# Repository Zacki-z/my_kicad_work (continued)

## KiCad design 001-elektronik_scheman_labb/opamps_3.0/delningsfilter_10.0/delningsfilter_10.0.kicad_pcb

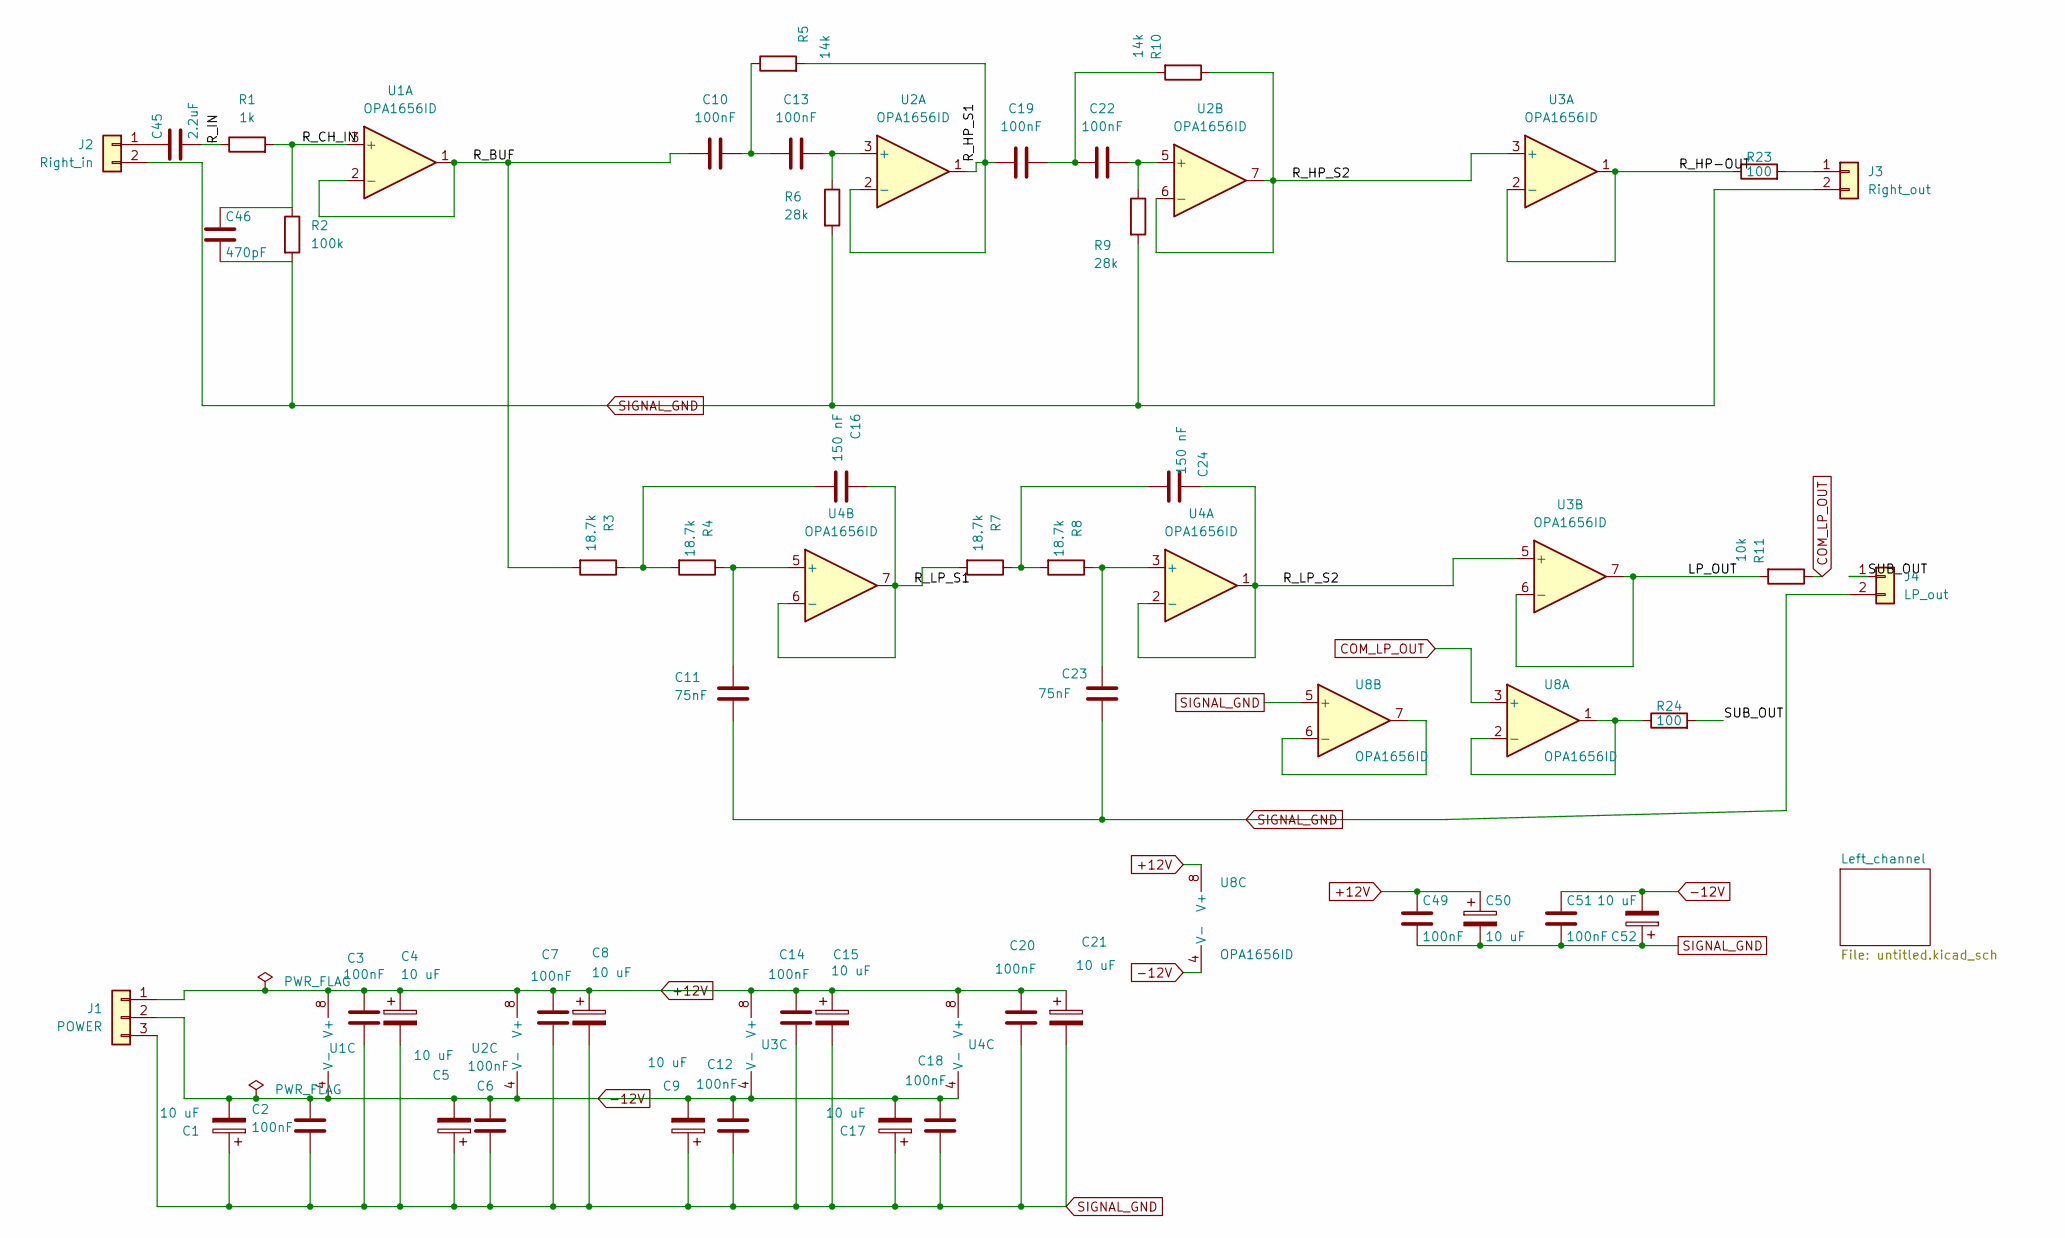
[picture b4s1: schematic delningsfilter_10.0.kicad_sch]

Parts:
C1, C4, C5, C8, C9, C15, C17, C21, C50, C52: 10 uF; CP_Radial_D5.0mm_P2.00mm
C2, C3, C6, C7, C10, C12, C13, C14, C18, C19, C20, C22, C49, C51: 100nF; C_Disc_D5.0mm_W2.5mm_P2.50mm
C11, C23: 75nF; C_Disc_D5.0mm_W2.5mm_P2.50mm
C16, C24: 150 nF; C_Disc_D5.0mm_W2.5mm_P2.50mm
C45: 2.2uF; C_Rect_L7.2mm_W3.5mm_P5.00mm_FKS2_FKP2_MKS2_MKP2
C46: 470pF; C_Disc_D5.0mm_W2.5mm_P2.50mm
J1: POWER; PinHeader_1x03_P2.54mm_Vertical; Part Number 1-0301FBV0T
J2: Right_in; PinHeader_1x02_P2.54mm_Vertical; Part Number 1-0201FBV0T
J3: Right_out; PinHeader_1x02_P2.54mm_Vertical; Part Number 1-0201FBV0T
J4: LP_out; PinHeader_1x02_P2.54mm_Vertical; Part Number 1-0201FBV0T
R1: 1k; R_Axial_DIN0207_L6.3mm_D2.5mm_P7.62mm_Horizontal
R2: 100k; R_Axial_DIN0207_L6.3mm_D2.5mm_P7.62mm_Horizontal
R3, R4, R7, R8: 18.7k; R_Axial_DIN0207_L6.3mm_D2.5mm_P7.62mm_Horizontal
R5, R10: 14k; R_Axial_DIN0207_L6.3mm_D2.5mm_P7.62mm_Horizontal
R6, R9: 28k; R_Axial_DIN0207_L6.3mm_D2.5mm_P7.62mm_Horizontal
R11: 10k; R_Axial_DIN0207_L6.3mm_D2.5mm_P7.62mm_Horizontal
R23, R24: 100; R_Axial_DIN0207_L6.3mm_D2.5mm_P7.62mm_Horizontal
U1, U2, U3, U4, U8: OPA1656ID; DIP-8_W7.62mm

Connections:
+12V: C3.1, C4.1, C7.1, C8.1, C14.1, C15.1, C20.1, C21.1, C49.1, C50.1, J1.1, U1.8 (V+), U2.8 (V+), U3.8 (V+), U4.8 (V+), U8.8 (V+); also elsewhere on the board
-12V: C1.2, C2.1, C5.2, C6.1, C9.2, C12.1, C17.2, C18.1, C51.1, C52.2, J1.2, U1.4 (V-), U2.4 (V-), U3.4 (V-), U4.4 (V-), U8.4 (V-); also elsewhere on the board
/LP_OUT: R11.2, U3.6 (-), U3.7
/R_BUF: C10.2, R3.2, U1.1, U1.2 (-)
/R_CH_IN: C46.1, R1.2, R2.1, U1.3 (+)
/R_HP-OUT: R23.1, U3.1, U3.2 (-)
/R_HP_S1: C19.2, R5.2, U2.1, U2.2 (-)
/R_HP_S2: R10.1, U2.6 (-), U2.7, U3.3 (+)
/R_IN: C45.2, R1.1
/R_LP_S1: C16.1, R7.2, U4.6 (-), U4.7
/R_LP_S2: C24.2, U3.5 (+), U4.1, U4.2 (-)
/SUB_OUT: J4.1, R24.2
COM_LP_OUT: R11.1, U8.3 (+); also elsewhere on the board
unnamed: C10.1, C13.2, R5.1
unnamed: C16.2, R3.1, R4.2
unnamed: C19.1, C22.2, R10.2
unnamed: C24.1, R7.1, R8.2
unnamed: C45.1, J2.1
unnamed: J3.1, R23.2
unnamed: C13.1, R6.1, U2.3 (+)
unnamed: C22.1, R9.1, U2.5 (+)
unnamed: C23.1, R8.1, U4.3 (+)
unnamed: C11.1, R4.1, U4.5 (+)
unnamed: R24.1, U8.1, U8.2 (-)
unnamed: U8.6 (-), U8.7
SIGNAL_GND: C1.1, C2.2, C3.2, C4.2, C5.1, C6.2, C7.2, C8.2, C9.1, C11.2, C12.2, C14.2, C15.2, C17.1, C18.2, C20.2, C21.2, C23.2, C46.2, C49.2, C50.2, C51.2, C52.1, J1.3, J2.2, J3.2, J4.2, R2.2, R6.2, R9.2, U8.5 (+); also elsewhere on the board

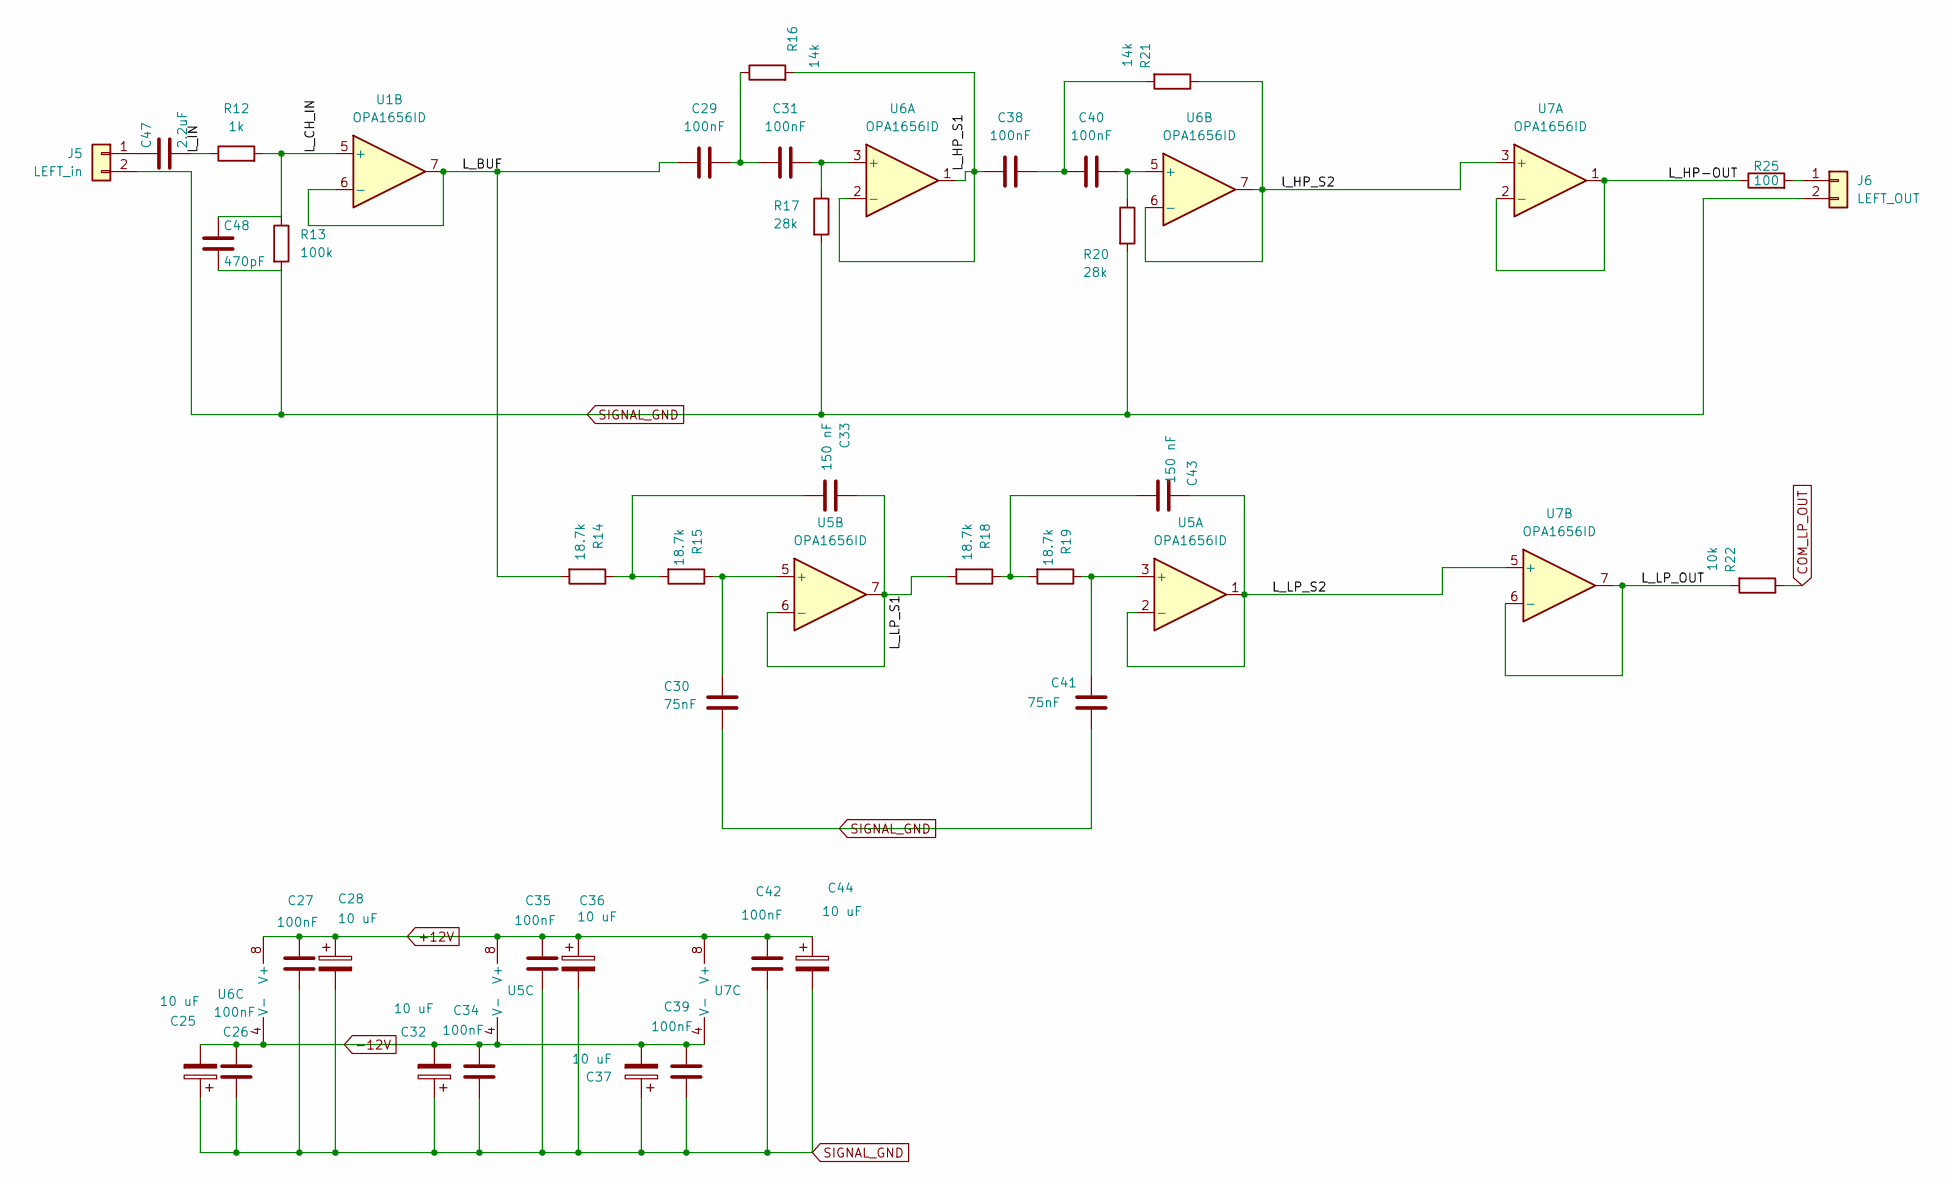
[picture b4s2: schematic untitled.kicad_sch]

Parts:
C25, C32, C36, C37, C44: 10 uF; CP_Radial_D5.0mm_P2.00mm
C26, C27, C29, C31, C34, C35, C38, C39, C40, C42: 100nF; C_Disc_D5.0mm_W2.5mm_P2.50mm
C28: 10 uF; CP_Radial_D5.0mm_P2.50mm
C30, C41: 75nF; C_Disc_D5.0mm_W2.5mm_P2.50mm
C33, C43: 150 nF; C_Disc_D5.0mm_W2.5mm_P2.50mm
C47: 2.2uF; C_Rect_L7.2mm_W3.5mm_P5.00mm_FKS2_FKP2_MKS2_MKP2
C48: 470pF; C_Disc_D5.0mm_W2.5mm_P2.50mm
J5: LEFT_in; PinHeader_1x02_P2.54mm_Vertical; Part Number 1-0201FBV0T
J6: LEFT_OUT; PinHeader_1x02_P2.54mm_Vertical; Part Number 1-0201FBV0T
R12: 1k; R_Axial_DIN0207_L6.3mm_D2.5mm_P7.62mm_Horizontal
R13: 100k; R_Axial_DIN0207_L6.3mm_D2.5mm_P7.62mm_Horizontal
R14, R15, R18, R19: 18.7k; R_Axial_DIN0207_L6.3mm_D2.5mm_P7.62mm_Horizontal
R16, R21: 14k; R_Axial_DIN0207_L6.3mm_D2.5mm_P7.62mm_Horizontal
R17, R20: 28k; R_Axial_DIN0207_L6.3mm_D2.5mm_P7.62mm_Horizontal
R22: 10k; R_Axial_DIN0207_L6.3mm_D2.5mm_P7.62mm_Horizontal
R25: 100; R_Axial_DIN0207_L6.3mm_D2.5mm_P7.62mm_Horizontal
U1, U5, U6, U7: OPA1656ID; DIP-8_W7.62mm

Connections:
+12V: C27.1, C28.1, C35.1, C36.1, C42.1, C44.1, U5.8 (V+), U6.8 (V+), U7.8 (V+); also elsewhere on the board
-12V: C25.2, C26.1, C32.2, C34.1, C37.2, C39.1, U5.4 (V-), U6.4 (V-), U7.4 (V-); also elsewhere on the board
/Left_channel/L_BUF: C29.2, R14.2, U1.6 (-), U1.7
/Left_channel/L_CH_IN: C48.1, R12.2, R13.1, U1.5 (+)
/Left_channel/L_HP-OUT: R25.1, U7.1, U7.2 (-)
/Left_channel/L_HP_S1: C38.2, R16.2, U6.1, U6.2 (-)
/Left_channel/L_IN: C47.2, R12.1
/Left_channel/L_LP_OUT: R22.2, U7.6 (-), U7.7
/Left_channel/L_LP_S1: C33.1, R18.2, U5.6 (-), U5.7
/Left_channel/L_LP_S2: C43.2, U5.1, U5.2 (-), U7.5 (+)
/Left_channel/l_HP_S2: R21.1, U6.6 (-), U6.7, U7.3 (+)
COM_LP_OUT: R22.1; also elsewhere on the board
unnamed: C29.1, C31.2, R16.1
unnamed: C33.2, R14.1, R15.2
unnamed: C38.1, C40.2, R21.2
unnamed: C43.1, R18.1, R19.2
unnamed: C47.1, J5.1
unnamed: J6.1, R25.2
unnamed: C41.1, R19.1, U5.3 (+)
unnamed: C30.1, R15.1, U5.5 (+)
unnamed: C31.1, R17.1, U6.3 (+)
unnamed: C40.1, R20.1, U6.5 (+)
SIGNAL_GND: C25.1, C26.2, C27.2, C28.2, C30.2, C32.1, C34.2, C35.2, C36.2, C37.1, C39.2, C41.2, C42.2, C44.2, C48.2, J5.2, J6.2, R13.2, R17.2, R20.2; also elsewhere on the board

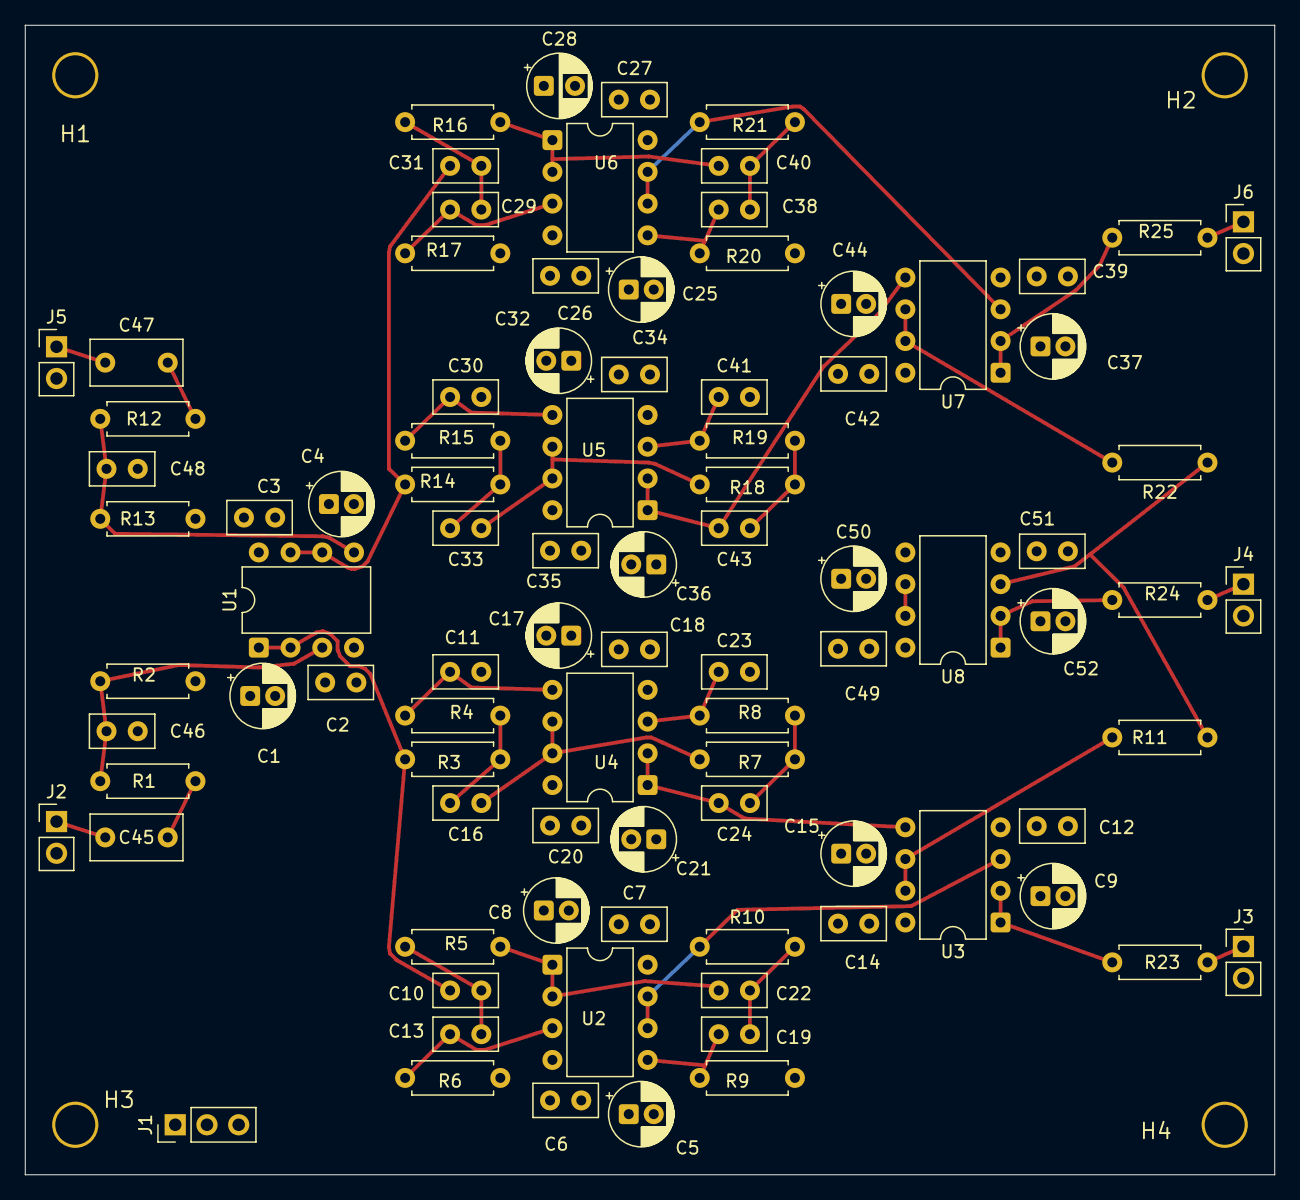
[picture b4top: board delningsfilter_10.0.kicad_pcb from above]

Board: 4 copper layers, 100.0 x 92.0 mm, 95 parts (0 on the bottom side), 45 nets.

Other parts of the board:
H1, H2, H3, H4: MountingHole; MountingHole_3.2mm

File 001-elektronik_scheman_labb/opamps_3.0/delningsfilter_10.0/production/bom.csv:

"Refs","Value","Footprint","Qty","DNP"
"C1","10 uF","Capacitor_THT:CP_Radial_D5.0mm_P2.00mm","1",""
"C2","100nF","Capacitor_THT:C_Disc_D5.0mm_W2.5mm_P2.50mm","1",""
"C3","100nF","Capacitor_THT:C_Disc_D5.0mm_W2.5mm_P2.50mm","1",""
"C4","10 uF","Capacitor_THT:CP_Radial_D5.0mm_P2.00mm","1",""
"C5","10 uF","Capacitor_THT:CP_Radial_D5.0mm_P2.00mm","1",""
"C6","100nF","Capacitor_THT:C_Disc_D5.0mm_W2.5mm_P2.50mm","1",""
"C7","100nF","Capacitor_THT:C_Disc_D5.0mm_W2.5mm_P2.50mm","1",""
"C8","10 uF","Capacitor_THT:CP_Radial_D5.0mm_P2.00mm","1",""
"C9","10 uF","Capacitor_THT:CP_Radial_D5.0mm_P2.00mm","1",""
"C10","100nF","Capacitor_THT:C_Disc_D5.0mm_W2.5mm_P2.50mm","1",""
"C11","75nF","Capacitor_THT:C_Disc_D5.0mm_W2.5mm_P2.50mm","1",""
"C12","100nF","Capacitor_THT:C_Disc_D5.0mm_W2.5mm_P2.50mm","1",""
"C13","100nF","Capacitor_THT:C_Disc_D5.0mm_W2.5mm_P2.50mm","1",""
"C14","100nF","Capacitor_THT:C_Disc_D5.0mm_W2.5mm_P2.50mm","1",""
"C15","10 uF","Capacitor_THT:CP_Radial_D5.0mm_P2.00mm","1",""
"C16","150 nF","Capacitor_THT:C_Disc_D5.0mm_W2.5mm_P2.50mm","1",""
"C17","10 uF","Capacitor_THT:CP_Radial_D5.0mm_P2.00mm","1",""
"C18","100nF","Capacitor_THT:C_Disc_D5.0mm_W2.5mm_P2.50mm","1",""
"C19","100nF","Capacitor_THT:C_Disc_D5.0mm_W2.5mm_P2.50mm","1",""
"C20","100nF","Capacitor_THT:C_Disc_D5.0mm_W2.5mm_P2.50mm","1",""
"C21","10 uF","Capacitor_THT:CP_Radial_D5.0mm_P2.00mm","1",""
"C22","100nF","Capacitor_THT:C_Disc_D5.0mm_W2.5mm_P2.50mm","1",""
"C23","75nF","Capacitor_THT:C_Disc_D5.0mm_W2.5mm_P2.50mm","1",""
"C24","150 nF","Capacitor_THT:C_Disc_D5.0mm_W2.5mm_P2.50mm","1",""
"C25","10 uF","Capacitor_THT:CP_Radial_D5.0mm_P2.00mm","1",""
"C26","100nF","Capacitor_THT:C_Disc_D5.0mm_W2.5mm_P2.50mm","1",""
"C27","100nF","Capacitor_THT:C_Disc_D5.0mm_W2.5mm_P2.50mm","1",""
"C28","10 uF","Capacitor_THT:CP_Radial_D5.0mm_P2.50mm","1",""
"C29","100nF","Capacitor_THT:C_Disc_D5.0mm_W2.5mm_P2.50mm","1",""
"C30","75nF","Capacitor_THT:C_Disc_D5.0mm_W2.5mm_P2.50mm","1",""
"C31","100nF","Capacitor_THT:C_Disc_D5.0mm_W2.5mm_P2.50mm","1",""
"C32","10 uF","Capacitor_THT:CP_Radial_D5.0mm_P2.00mm","1",""
"C33","150 nF","Capacitor_THT:C_Disc_D5.0mm_W2.5mm_P2.50mm","1",""
"C34","100nF","Capacitor_THT:C_Disc_D5.0mm_W2.5mm_P2.50mm","1",""
"C35","100nF","Capacitor_THT:C_Disc_D5.0mm_W2.5mm_P2.50mm","1",""
"C36","10 uF","Capacitor_THT:CP_Radial_D5.0mm_P2.00mm","1",""
"C37","10 uF","Capacitor_THT:CP_Radial_D5.0mm_P2.00mm","1",""
"C38","100nF","Capacitor_THT:C_Disc_D5.0mm_W2.5mm_P2.50mm","1",""
"C39","100nF","Capacitor_THT:C_Disc_D5.0mm_W2.5mm_P2.50mm","1",""
"C40","100nF","Capacitor_THT:C_Disc_D5.0mm_W2.5mm_P2.50mm","1",""
"C41","75nF","Capacitor_THT:C_Disc_D5.0mm_W2.5mm_P2.50mm","1",""
"C42","100nF","Capacitor_THT:C_Disc_D5.0mm_W2.5mm_P2.50mm","1",""
"C43","150 nF","Capacitor_THT:C_Disc_D5.0mm_W2.5mm_P2.50mm","1",""
"C44","10 uF","Capacitor_THT:CP_Radial_D5.0mm_P2.00mm","1",""
"C45","2.2uF","Capacitor_THT:C_Rect_L7.2mm_W3.5mm_P5.00mm_FKS2_FKP2_MKS2_MKP2","1",""
"C46","470pF","Capacitor_THT:C_Disc_D5.0mm_W2.5mm_P2.50mm","1",""
"C47","2.2uF","Capacitor_THT:C_Rect_L7.2mm_W3.5mm_P5.00mm_FKS2_FKP2_MKS2_MKP2","1",""
"C48","470pF","Capacitor_THT:C_Disc_D5.0mm_W2.5mm_P2.50mm","1",""
"C49","100nF","Capacitor_THT:C_Disc_D5.0mm_W2.5mm_P2.50mm","1",""
"C50","10 uF","Capacitor_THT:CP_Radial_D5.0mm_P2.00mm","1",""
"C51","100nF","Capacitor_THT:C_Disc_D5.0mm_W2.5mm_P2.50mm","1",""
"C52","10 uF","Capacitor_THT:CP_Radial_D5.0mm_P2.00mm","1",""
"J1","POWER","Connector_PinHeader_2.54mm:PinHeader_1x03_P2.54mm_Vertical","1",""
"J2","Right_in","Connector_PinHeader_2.54mm:PinHeader_1x02_P2.54mm_Vertical","1",""
"J3","Right_out","Connector_PinHeader_2.54mm:PinHeader_1x02_P2.54mm_Vertical","1",""
"J4","LP_out","Connector_PinHeader_2.54mm:PinHeader_1x02_P2.54mm_Vertical","1",""
"J5","LEFT_in","Connector_PinHeader_2.54mm:PinHeader_1x02_P2.54mm_Vertical","1",""
"J6","LEFT_OUT","Connector_PinHeader_2.54mm:PinHeader_1x02_P2.54mm_Vertical","1",""
"R1","1k","Resistor_THT:R_Axial_DIN0207_L6.3mm_D2.5mm_P7.62mm_Horizontal","1",""
"R2","100k","Resistor_THT:R_Axial_DIN0207_L6.3mm_D2.5mm_P7.62mm_Horizontal","1",""
"R3","18.7k","Resistor_THT:R_Axial_DIN0207_L6.3mm_D2.5mm_P7.62mm_Horizontal","1",""
"R4","18.7k","Resistor_THT:R_Axial_DIN0207_L6.3mm_D2.5mm_P7.62mm_Horizontal","1",""
"R5","14k","Resistor_THT:R_Axial_DIN0207_L6.3mm_D2.5mm_P7.62mm_Horizontal","1",""
"R6","28k","Resistor_THT:R_Axial_DIN0207_L6.3mm_D2.5mm_P7.62mm_Horizontal","1",""
"R7","18.7k","Resistor_THT:R_Axial_DIN0207_L6.3mm_D2.5mm_P7.62mm_Horizontal","1",""
"R8","18.7k","Resistor_THT:R_Axial_DIN0207_L6.3mm_D2.5mm_P7.62mm_Horizontal","1",""
"R9","28k","Resistor_THT:R_Axial_DIN0207_L6.3mm_D2.5mm_P7.62mm_Horizontal","1",""
"R10","14k","Resistor_THT:R_Axial_DIN0207_L6.3mm_D2.5mm_P7.62mm_Horizontal","1",""
"R11","10k","Resistor_THT:R_Axial_DIN0207_L6.3mm_D2.5mm_P7.62mm_Horizontal","1",""
"R12","1k","Resistor_THT:R_Axial_DIN0207_L6.3mm_D2.5mm_P7.62mm_Horizontal","1",""
"R13","100k","Resistor_THT:R_Axial_DIN0207_L6.3mm_D2.5mm_P7.62mm_Horizontal","1",""
"R14","18.7k","Resistor_THT:R_Axial_DIN0207_L6.3mm_D2.5mm_P7.62mm_Horizontal","1",""
"R15","18.7k","Resistor_THT:R_Axial_DIN0207_L6.3mm_D2.5mm_P7.62mm_Horizontal","1",""
"R16","14k","Resistor_THT:R_Axial_DIN0207_L6.3mm_D2.5mm_P7.62mm_Horizontal","1",""
"R17","28k","Resistor_THT:R_Axial_DIN0207_L6.3mm_D2.5mm_P7.62mm_Horizontal","1",""
"R18","18.7k","Resistor_THT:R_Axial_DIN0207_L6.3mm_D2.5mm_P7.62mm_Horizontal","1",""
"R19","18.7k","Resistor_THT:R_Axial_DIN0207_L6.3mm_D2.5mm_P7.62mm_Horizontal","1",""
"R20","28k","Resistor_THT:R_Axial_DIN0207_L6.3mm_D2.5mm_P7.62mm_Horizontal","1",""
"R21","14k","Resistor_THT:R_Axial_DIN0207_L6.3mm_D2.5mm_P7.62mm_Horizontal","1",""
"R22","10k","Resistor_THT:R_Axial_DIN0207_L6.3mm_D2.5mm_P7.62mm_Horizontal","1",""
"R23","100","Resistor_THT:R_Axial_DIN0207_L6.3mm_D2.5mm_P7.62mm_Horizontal","1",""
"R24","100","Resistor_THT:R_Axial_DIN0207_L6.3mm_D2.5mm_P7.62mm_Horizontal","1",""
"R25","100","Resistor_THT:R_Axial_DIN0207_L6.3mm_D2.5mm_P7.62mm_Horizontal","1",""
"U1","OPA1656ID","Package_DIP:DIP-8_W7.62mm","1",""
"U2","OPA1656ID","Package_DIP:DIP-8_W7.62mm","1",""
"U3","OPA1656ID","Package_DIP:DIP-8_W7.62mm","1",""
"U4","OPA1656ID","Package_DIP:DIP-8_W7.62mm","1",""
"U5","OPA1656ID","Package_DIP:DIP-8_W7.62mm","1",""
"U6","OPA1656ID","Package_DIP:DIP-8_W7.62mm","1",""
"U7","OPA1656ID","Package_DIP:DIP-8_W7.62mm","1",""
"U8","OPA1656ID","Package_DIP:DIP-8_W7.62mm","1",""

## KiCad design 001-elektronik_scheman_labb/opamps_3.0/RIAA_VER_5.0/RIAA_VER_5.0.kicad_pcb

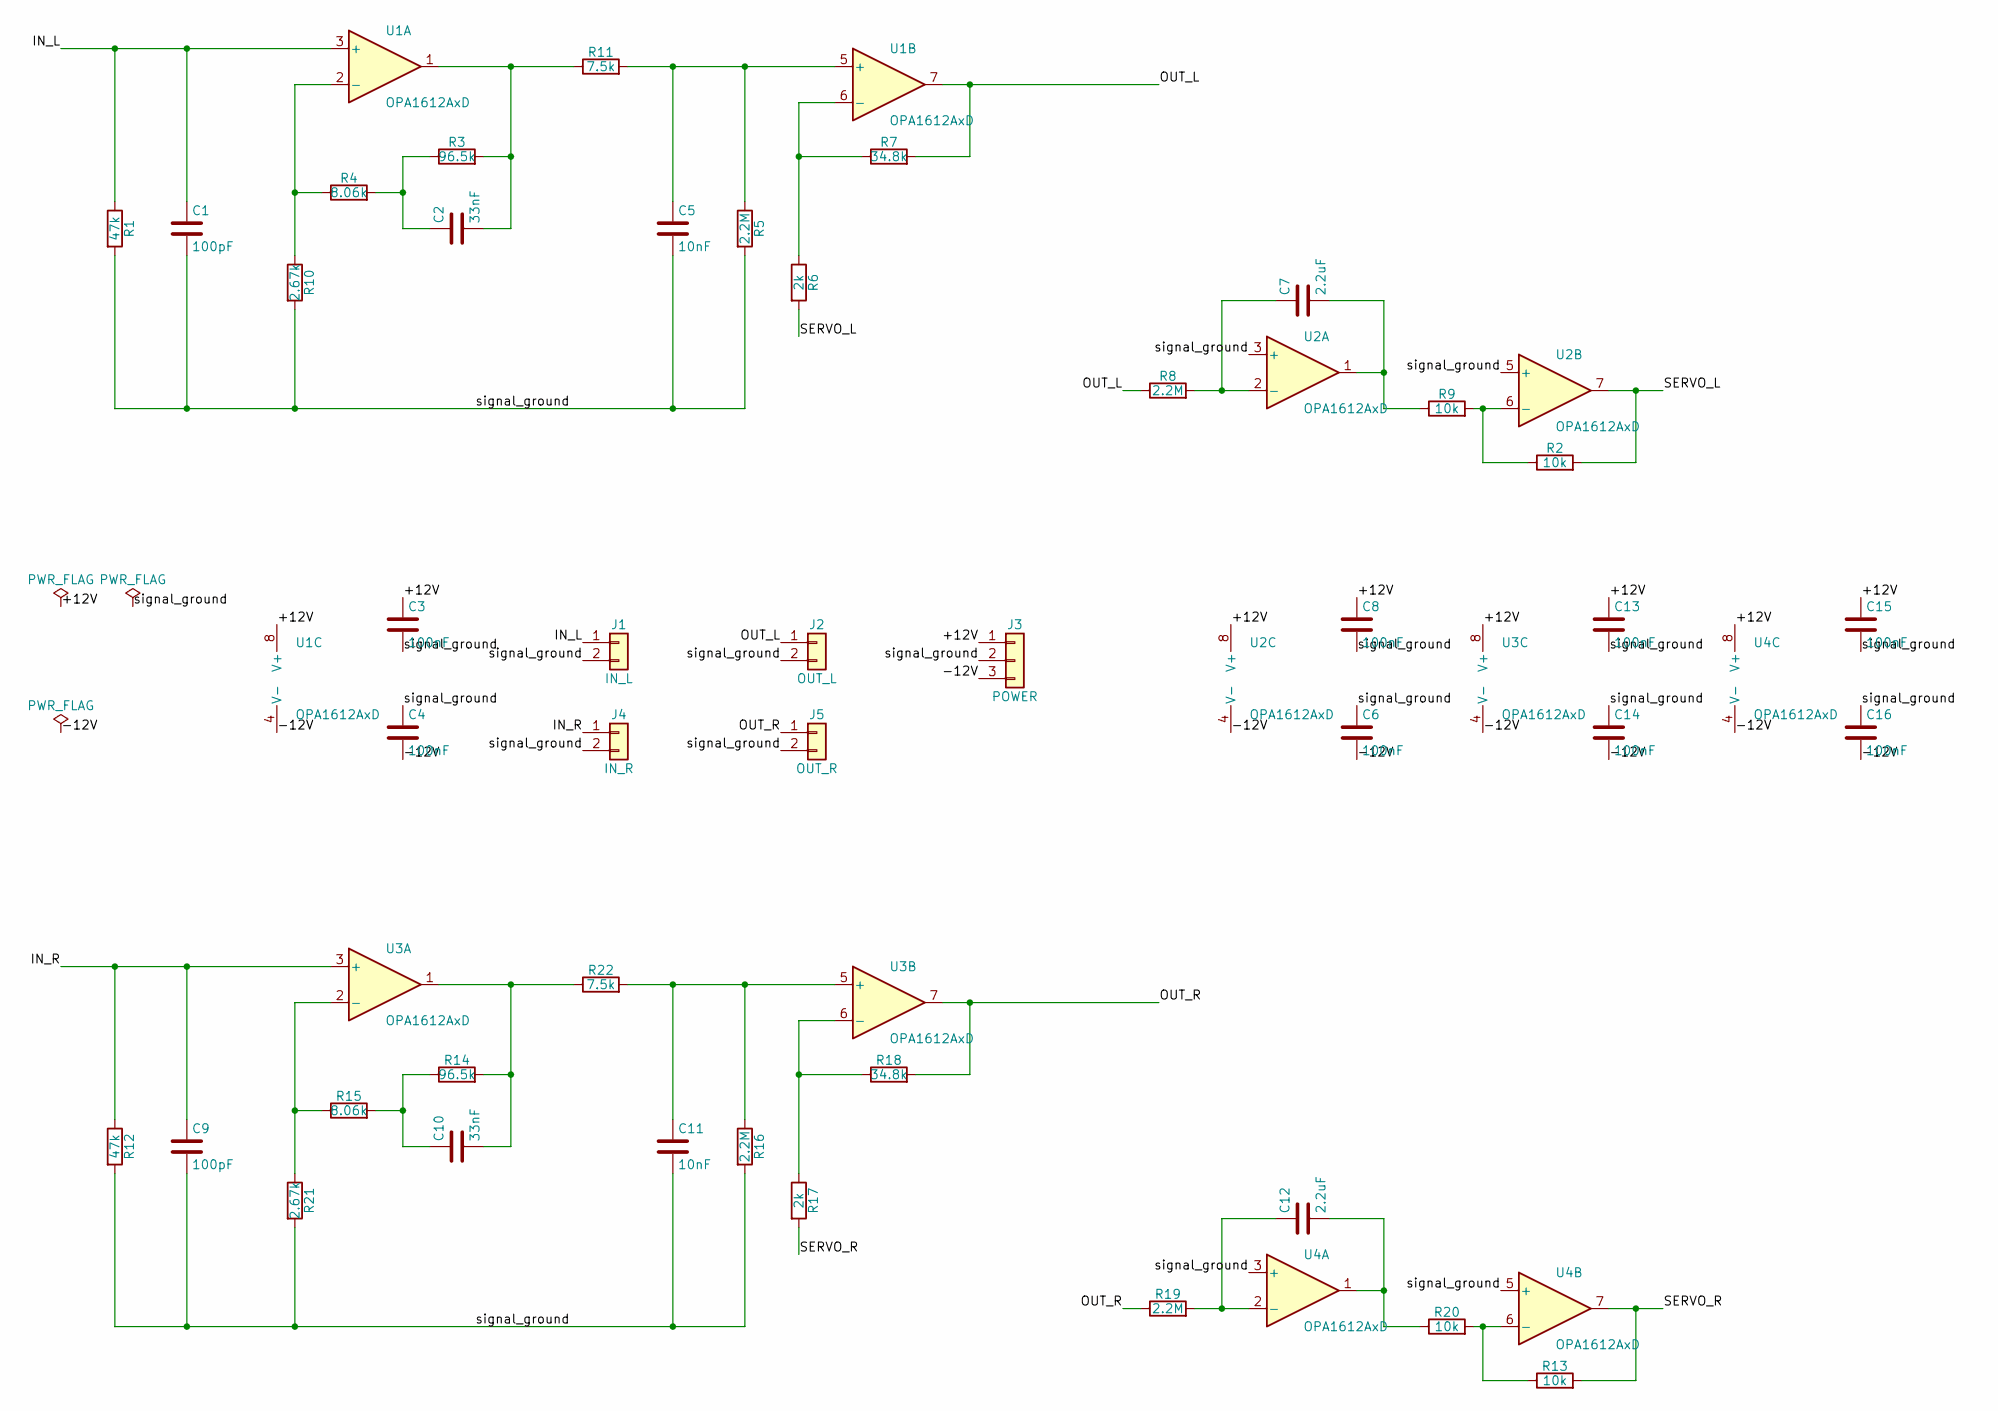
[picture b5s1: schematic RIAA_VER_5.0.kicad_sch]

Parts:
C1, C9: 100pF; C_Disc_D5.0mm_W2.5mm_P2.50mm
C2, C10: 33nF; C_Rect_L7.2mm_W3.5mm_P5.00mm_FKS2_FKP2_MKS2_MKP2
C3, C4, C6, C8, C13, C14, C15, C16: 100nF; C_Disc_D5.0mm_W2.5mm_P2.50mm
C5, C11: 10nF; C_Rect_L7.2mm_W3.5mm_P5.00mm_FKS2_FKP2_MKS2_MKP2
C7, C12: 2.2uF; C_Rect_L7.2mm_W5.5mm_P5.00mm_FKS2_FKP2_MKS2_MKP2
J1: IN_L; PinHeader_1x02_P2.54mm_Vertical
J2: OUT_L; PinHeader_1x02_P2.54mm_Vertical
J3: POWER; PinHeader_1x03_P2.54mm_Vertical
J4: IN_R; PinHeader_1x02_P2.54mm_Vertical
J5: OUT_R; PinHeader_1x02_P2.54mm_Vertical
R1, R12: 47k; R_Axial_DIN0207_L6.3mm_D2.5mm_P7.62mm_Horizontal
R2, R9, R13, R20: 10k; R_Axial_DIN0207_L6.3mm_D2.5mm_P7.62mm_Horizontal
R3, R14: 96.5k; R_Axial_DIN0207_L6.3mm_D2.5mm_P7.62mm_Horizontal
R4, R15: 8.06k; R_Axial_DIN0207_L6.3mm_D2.5mm_P7.62mm_Horizontal
R5, R8, R16, R19: 2.2M; R_Axial_DIN0207_L6.3mm_D2.5mm_P7.62mm_Horizontal
R6, R17: 2k; R_Axial_DIN0207_L6.3mm_D2.5mm_P7.62mm_Horizontal
R7, R18: 34.8k; R_Axial_DIN0207_L6.3mm_D2.5mm_P7.62mm_Horizontal
R10, R21: 2.67k; R_Axial_DIN0207_L6.3mm_D2.5mm_P7.62mm_Horizontal
R11, R22: 7.5k; R_Axial_DIN0207_L6.3mm_D2.5mm_P7.62mm_Horizontal
U1, U2, U3, U4: OPA1612AxD; DIP-8_W7.62mm

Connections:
/+12V: C3.1, C8.1, C13.1, C15.1, J3.1, U1.8 (V+), U2.8 (V+), U3.8 (V+), U4.8 (V+)
/-12V: C4.2, C6.2, C14.2, C16.2, J3.3, U1.4 (V-), U2.4 (V-), U3.4 (V-), U4.4 (V-)
/IN_L: C1.1, J1.1, R1.1, U1.3 (+)
/IN_R: C9.1, J4.1, R12.1, U3.3 (+)
/OUT_L: J2.1, R7.2, R8.1, U1.7
/OUT_R: J5.1, R18.2, R19.1, U3.7
/SERVO_L: R2.2, R6.2, U2.7
/SERVO_R: R13.2, R17.2, U4.7
/signal_ground: C1.2, C3.2, C4.1, C5.2, C6.1, C8.2, C9.2, C11.2, C13.2, C14.1, C15.2, C16.1, J1.2, J2.2, J3.2, J4.2, J5.2, R1.2, R5.2, R10.2, R12.2, R16.2, R21.2, U2.3 (+), U2.5 (+), U4.3 (+), U4.5 (+)
unnamed: C2.1, R3.1, R4.2
unnamed: C2.2, R3.2, R11.1, U1.1
unnamed: C7.2, R9.1, U2.1
unnamed: C10.1, R14.1, R15.2
unnamed: C10.2, R14.2, R22.1, U3.1
unnamed: C12.2, R20.1, U4.1
unnamed: R4.1, R10.1, U1.2 (-)
unnamed: C5.1, R5.1, R11.2, U1.5 (+)
unnamed: R6.1, R7.1, U1.6 (-)
unnamed: C7.1, R8.2, U2.2 (-)
unnamed: R2.1, R9.2, U2.6 (-)
unnamed: R15.1, R21.1, U3.2 (-)
unnamed: C11.1, R16.1, R22.2, U3.5 (+)
unnamed: R17.1, R18.1, U3.6 (-)
unnamed: C12.1, R19.2, U4.2 (-)
unnamed: R13.1, R20.2, U4.6 (-)

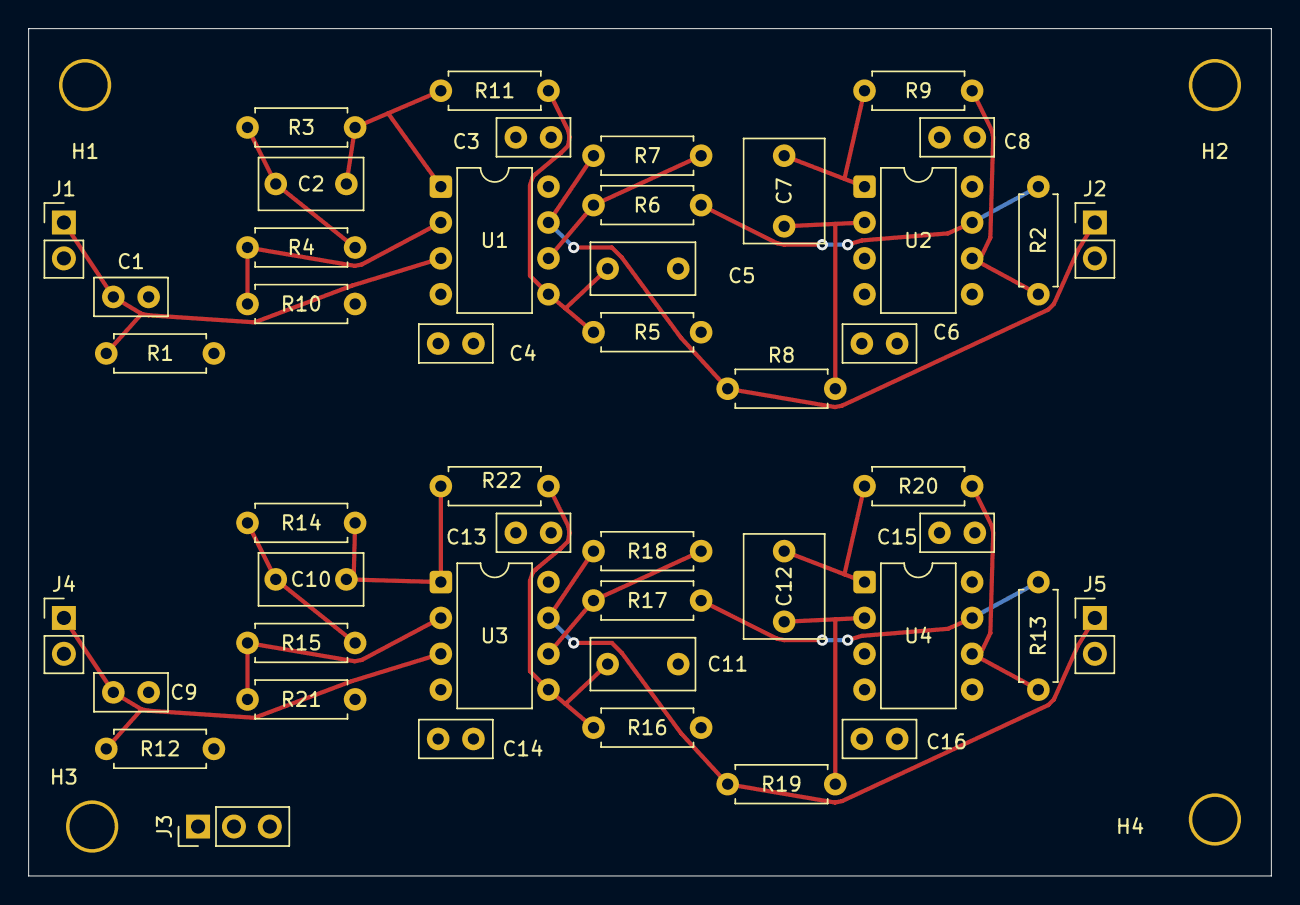
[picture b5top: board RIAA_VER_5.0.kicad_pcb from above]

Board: 4 copper layers, 88.0 x 60.0 mm, 51 parts (0 on the bottom side), 25 nets.

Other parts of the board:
H1, H2, H3, H4: MountingHole; MountingHole_3.2mm

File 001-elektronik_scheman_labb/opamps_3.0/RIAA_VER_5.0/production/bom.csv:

"Refs","Value","Footprint","Qty","DNP"
"C1","100pF","Capacitor_THT:C_Disc_D5.0mm_W2.5mm_P2.50mm","1",""
"C2","33nF","Capacitor_THT:C_Rect_L7.2mm_W3.5mm_P5.00mm_FKS2_FKP2_MKS2_MKP2","1",""
"C3","100nF","Capacitor_THT:C_Disc_D5.0mm_W2.5mm_P2.50mm","1",""
"C4","100nF","Capacitor_THT:C_Disc_D5.0mm_W2.5mm_P2.50mm","1",""
"C5","10nF","Capacitor_THT:C_Rect_L7.2mm_W3.5mm_P5.00mm_FKS2_FKP2_MKS2_MKP2","1",""
"C6","100nF","Capacitor_THT:C_Disc_D5.0mm_W2.5mm_P2.50mm","1",""
"C7","2.2uF","Capacitor_THT:C_Rect_L7.2mm_W5.5mm_P5.00mm_FKS2_FKP2_MKS2_MKP2","1",""
"C8","100nF","Capacitor_THT:C_Disc_D5.0mm_W2.5mm_P2.50mm","1",""
"C9","100pF","Capacitor_THT:C_Disc_D5.0mm_W2.5mm_P2.50mm","1",""
"C10","33nF","Capacitor_THT:C_Rect_L7.2mm_W3.5mm_P5.00mm_FKS2_FKP2_MKS2_MKP2","1",""
"C11","10nF","Capacitor_THT:C_Rect_L7.2mm_W3.5mm_P5.00mm_FKS2_FKP2_MKS2_MKP2","1",""
"C12","2.2uF","Capacitor_THT:C_Rect_L7.2mm_W5.5mm_P5.00mm_FKS2_FKP2_MKS2_MKP2","1",""
"C13","100nF","Capacitor_THT:C_Disc_D5.0mm_W2.5mm_P2.50mm","1",""
"C14","100nF","Capacitor_THT:C_Disc_D5.0mm_W2.5mm_P2.50mm","1",""
"C15","100nF","Capacitor_THT:C_Disc_D5.0mm_W2.5mm_P2.50mm","1",""
"C16","100nF","Capacitor_THT:C_Disc_D5.0mm_W2.5mm_P2.50mm","1",""
"J1","IN_L","Connector_PinHeader_2.54mm:PinHeader_1x02_P2.54mm_Vertical","1",""
"J2","OUT_L","Connector_PinHeader_2.54mm:PinHeader_1x02_P2.54mm_Vertical","1",""
"J3","POWER","Connector_PinHeader_2.54mm:PinHeader_1x03_P2.54mm_Vertical","1",""
"J4","IN_R","Connector_PinHeader_2.54mm:PinHeader_1x02_P2.54mm_Vertical","1",""
"J5","OUT_R","Connector_PinHeader_2.54mm:PinHeader_1x02_P2.54mm_Vertical","1",""
"R1","47k","Resistor_THT:R_Axial_DIN0207_L6.3mm_D2.5mm_P7.62mm_Horizontal","1",""
"R2","10k","Resistor_THT:R_Axial_DIN0207_L6.3mm_D2.5mm_P7.62mm_Horizontal","1",""
"R3","96.5k","Resistor_THT:R_Axial_DIN0207_L6.3mm_D2.5mm_P7.62mm_Horizontal","1",""
"R4","8.06k","Resistor_THT:R_Axial_DIN0207_L6.3mm_D2.5mm_P7.62mm_Horizontal","1",""
"R5","2.2M","Resistor_THT:R_Axial_DIN0207_L6.3mm_D2.5mm_P7.62mm_Horizontal","1",""
"R6","2k","Resistor_THT:R_Axial_DIN0207_L6.3mm_D2.5mm_P7.62mm_Horizontal","1",""
"R7","34.8k","Resistor_THT:R_Axial_DIN0207_L6.3mm_D2.5mm_P7.62mm_Horizontal","1",""
"R8","2.2M","Resistor_THT:R_Axial_DIN0207_L6.3mm_D2.5mm_P7.62mm_Horizontal","1",""
"R9","10k","Resistor_THT:R_Axial_DIN0207_L6.3mm_D2.5mm_P7.62mm_Horizontal","1",""
"R10","2.67k","Resistor_THT:R_Axial_DIN0207_L6.3mm_D2.5mm_P7.62mm_Horizontal","1",""
"R11","7.5k","Resistor_THT:R_Axial_DIN0207_L6.3mm_D2.5mm_P7.62mm_Horizontal","1",""
"R12","47k","Resistor_THT:R_Axial_DIN0207_L6.3mm_D2.5mm_P7.62mm_Horizontal","1",""
"R13","10k","Resistor_THT:R_Axial_DIN0207_L6.3mm_D2.5mm_P7.62mm_Horizontal","1",""
"R14","96.5k","Resistor_THT:R_Axial_DIN0207_L6.3mm_D2.5mm_P7.62mm_Horizontal","1",""
"R15","8.06k","Resistor_THT:R_Axial_DIN0207_L6.3mm_D2.5mm_P7.62mm_Horizontal","1",""
"R16","2.2M","Resistor_THT:R_Axial_DIN0207_L6.3mm_D2.5mm_P7.62mm_Horizontal","1",""
"R17","2k","Resistor_THT:R_Axial_DIN0207_L6.3mm_D2.5mm_P7.62mm_Horizontal","1",""
"R18","34.8k","Resistor_THT:R_Axial_DIN0207_L6.3mm_D2.5mm_P7.62mm_Horizontal","1",""
"R19","2.2M","Resistor_THT:R_Axial_DIN0207_L6.3mm_D2.5mm_P7.62mm_Horizontal","1",""
"R20","10k","Resistor_THT:R_Axial_DIN0207_L6.3mm_D2.5mm_P7.62mm_Horizontal","1",""
"R21","2.67k","Resistor_THT:R_Axial_DIN0207_L6.3mm_D2.5mm_P7.62mm_Horizontal","1",""
"R22","7.5k","Resistor_THT:R_Axial_DIN0207_L6.3mm_D2.5mm_P7.62mm_Horizontal","1",""
"U1","OPA1612AxD","Package_DIP:DIP-8_W7.62mm","1",""
"U2","OPA1612AxD","Package_DIP:DIP-8_W7.62mm","1",""
"U3","OPA1612AxD","Package_DIP:DIP-8_W7.62mm","1",""
"U4","OPA1612AxD","Package_DIP:DIP-8_W7.62mm","1",""

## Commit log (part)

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2026-01-17 CCS_stuff
2026-01-17 CCS-ver4
2026-01-19 princip scheman
2026-01-24 triodlabb
2026-01-24 Add shuntmätning (opamp + A0 filter + OLED code)
2026-02-08 Ignore KiCad/LibreOffice autosave, lock, and backup files
2026-02-08 Update gridvoltage_vario schematic
2026-02-08 Add new KiCad projects: Styra_inspänning and gainclone
2026-02-10 op-amp-labb
